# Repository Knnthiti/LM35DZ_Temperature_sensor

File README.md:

# Zero and Span Adjustment Circuit for LM35 Temperature Sensor

โปรเจกต์นี้เป็นการออกแบบและสร้างวงจรปรับแต่งสัญญาณ (Signal Conditioning) เพื่อแปลงแรงดันจากเซนเซอร์ **LM35** ให้เหมาะสมกับ ADC ของ Microcontroller โดยค่าที่ได้จากการทดลองอยู่ในช่วงประมาณ **0.218V – 0.507V** และแปลงเป็นค่า ADC ได้ประมาณ **0.64 – 3.10**

## 📐 รายละเอียดการคำนวณ (Calculation)

ข้อมูลในหัวข้อนี้อ้างอิงจาก **ผลการทดลองจริง** โดยสามารถดูแหล่งข้อมูลได้จากไฟล์ **กราฟการทดลอง.xlsx**

### 1. วิเคราะห์สัญญาณขาเข้า (Input Analysis)
ค่าที่วัดได้จากการทดลองจริงมีดังนี้:

| อุณหภูมิ (°C) | แรงดัน (V) | ADC |
|---:|---:|---:|
| 50 | 0.507 | 3.10 |
| 45 | 0.454 | 2.82 |
| 40 | 0.403 | 2.35 |
| 35 | 0.355 | 1.94 |
| 30 | 0.312 | 1.51 |
| 25 | 0.253 | 1.00 |
| 20 | 0.218 | 0.64 |

### 2. สมการเส้นตรง (Transfer Function)
ใช้รูปแบบสมการเส้นตรงแบบเดิมคือ
$$y = mx + c$$

โดย
- $m$ คือความชัน (Slope)
- $c$ คือจุดตัดแกน $y$ (Offset)

**2.1 การหาสมการ V_to_ADC**

กำหนดให้ $x = V$ และ $y = ADC$

- แทนค่าจากข้อมูลจริงในไฟล์ **กราฟการทดลอง.xlsx** (ใช้จุดปลายช่วงวัด)
  - จุดที่ 1: $(V, ADC) = (0.218, 0.64)$
  - จุดที่ 2: $(V, ADC) = (0.507, 3.10)$

- **หาค่าความชัน (Slope) แบบเดิม:**
  $$m = \frac{\Delta ADC}{\Delta V} = \frac{3.10 - 0.64}{0.507 - 0.218} = \frac{2.46}{0.289} = 8.5121$$

- **หาค่าออฟเซต (Intercept):**
  แทนค่าใน $y = mx + c$ ด้วยจุด $(0.218, 0.64)$
  $$0.64 = (8.5121 \times 0.218) + c$$
  $$0.64 = 1.8556 + c$$
  $$c = 0.64 - 1.8556 = -1.2156$$

- ตรวจสอบกับเส้นแนวโน้ม (Linear Trendline) จะได้ค่าเดียวกันคือ
  $$m = 8.5121,\; c = -1.2156$$

ดังนั้นสมการคือ
$$ADC = 8.5121V - 1.2156$$

**2.2 การหาสมการ ADC_to_C**

กำหนดให้ $x = ADC$ และ $y = C$

- จากการทำเส้นแนวโน้ม (Linear Trendline) ในไฟล์ **กราฟการทดลอง.xlsx** ได้ค่า
  $$m = 11.336,\; c = 13.106$$

ดังนั้นสมการคือ
$$C = 11.336(ADC) + 13.106$$

**สรุปสมการจากข้อมูลทดลองจริง (พร้อมกราฟ):**

1. **V_to_ADC**
   $$ADC = 8.5121V - 1.2156$$

2. **ADC_to_C**
   $$C = 11.336(ADC) + 13.106$$

จากภาพด้านบน ค่าที่ใช้ใน README เป็นค่าจริงจากการทดลอง และสามารถตรวจสอบรายละเอียดได้จากไฟล์ **กราฟการทดลอง.xlsx**

---

## 🛠 โครงสร้างและการทำงานของวงจร

วงจรนี้ใช้ Op-Amp **LM358** ในการจัดการสัญญาณ แบ่งออกเป็นส่วนต่างๆ ดังนี้:

- **Sensor Input:** รับสัญญาณจาก LM35-LP ที่ไฟเลี้ยง 3.3V
- **Input Buffer (U2A):** ทำหน้าที่เป็น Voltage Follower เพื่อแยกโหลดออกจากตัวเซนเซอร์
- **Zero Adjustment (U3A):** ใช้ Potentiometer (RV1) เพื่อปรับแรงดันอ้างอิง (Reference Voltage) สำหรับชดเชยค่า Offset
- **Span Adjustment (U3B):** ปรับอัตราขยาย (Gain) เพื่อให้ได้ช่วงแรงดันที่ต้องการ (Span)
- **Output:** สัญญาณ $V_{out}$ จะถูกส่งออกทาง Connector J1

## 📊 ระบบแสดงข้อมูล (Display System)

ระบบแสดงผลถูกแบ่งเป็น 3 โหมดตามปุ่มควบคุม ดังนี้:
- **ปุ่มซ้าย:** เข้าโหมด **WiFi Manager** และเมื่อเชื่อมต่อเครือข่ายสำเร็จ ระบบจะแสดง **IP Address** สำหรับเชื่อมต่อผ่าน **WebSocket**
- **ปุ่มกลาง:** แสดงค่า **อุณหภูมิ** ที่วัดได้จากเซนเซอร์
- **ปุ่มขวา:** แสดงค่า **แรงดันไฟฟ้า** ของสัญญาณที่วัดได้

เป็น Zero and span adjustment circuit :
- **R ตัวบน:** เป็น Rf ปรับกำลังขยาย
- **R ตัวล่าง:** เป็น span ปรับแรงดัน

โค้ดโปรแกรมสามารถดูได้ที่ไฟล์ `T_sensor_V3/T_sensor_V3.ino`

---

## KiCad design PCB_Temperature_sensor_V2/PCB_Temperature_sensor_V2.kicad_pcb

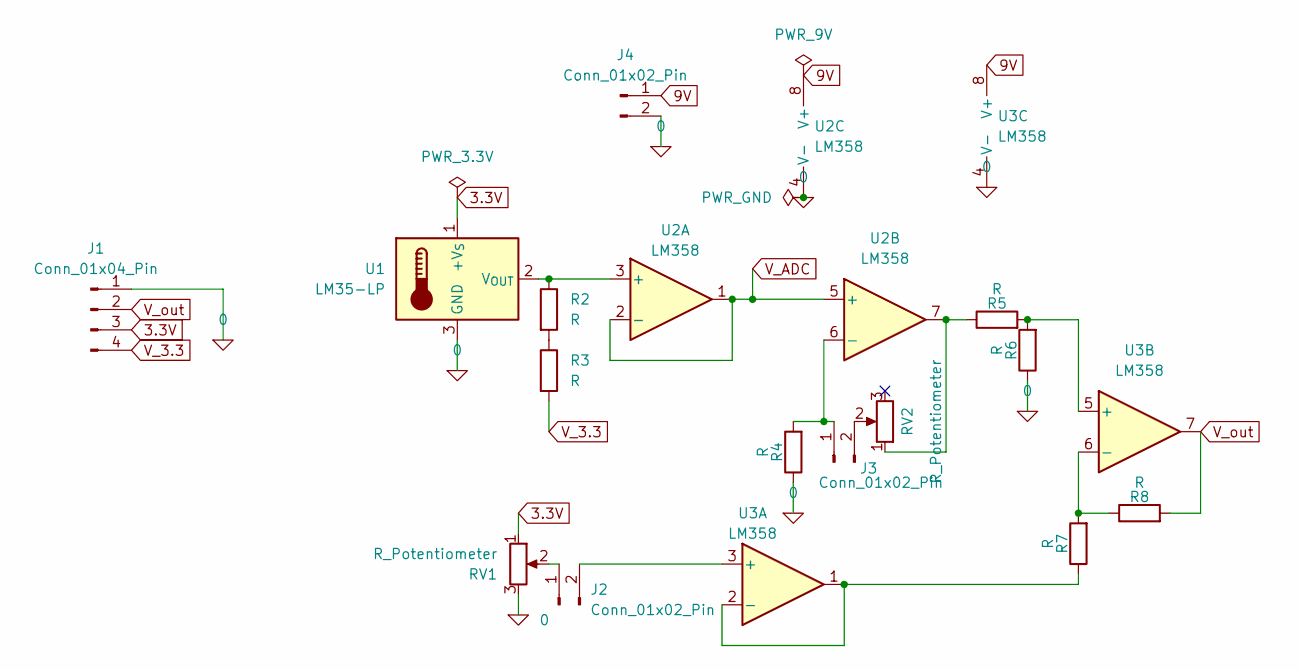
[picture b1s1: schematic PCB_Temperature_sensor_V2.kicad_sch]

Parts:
J1: Conn_01x04_Pin; PinSocket_1x04_P2.54mm_Vertical
J2, J3, J4: Conn_01x02_Pin; PinHeader_1x02_P2.54mm_Vertical
R2, R3: R; R_Axial_DIN0207_L6.3mm_D2.5mm_P7.62mm_Horizontal
R4, R5, R6, R7, R8: R; R_0603_1608Metric_Pad0.98x0.95mm_HandSolder
RV1, RV2: R_Potentiometer; Potentiometer_Piher_PT-10-V10_Vertical
U1: LM35-LP; TO-92_Inline
U2, U3: LM358; DIP-8_W7.62mm

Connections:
0: J1.1, J4.2, R4.1, R6.1, RV1.3, U1.3 (GND), U2.4 (V-), U3.4 (V-)
3.3V: J1.3, RV1.1, U1.1 (+V_{S})
9V: J4.1, U2.8 (V+), U3.8 (V+)
unnamed: J2.1, RV1.2
unnamed: J2.2, U3.3 (+)
unnamed: J3.1, R4.2, U2.6 (-)
unnamed: J3.2, RV2.2
unnamed: R2.2, R3.1
unnamed: R5.1, RV2.1, U2.7
unnamed: R2.1, U1.2 (V_{OUT}), U2.3 (+)
unnamed: R7.1, U3.1, U3.2 (-)
unnamed: R5.2, R6.2, U3.5 (+)
unnamed: R7.2, R8.1, U3.6 (-)
V_3.3: J1.4, R3.2
V_ADC: U2.1, U2.2 (-), U2.5 (+)
V_out: J1.2, R8.2, U3.7

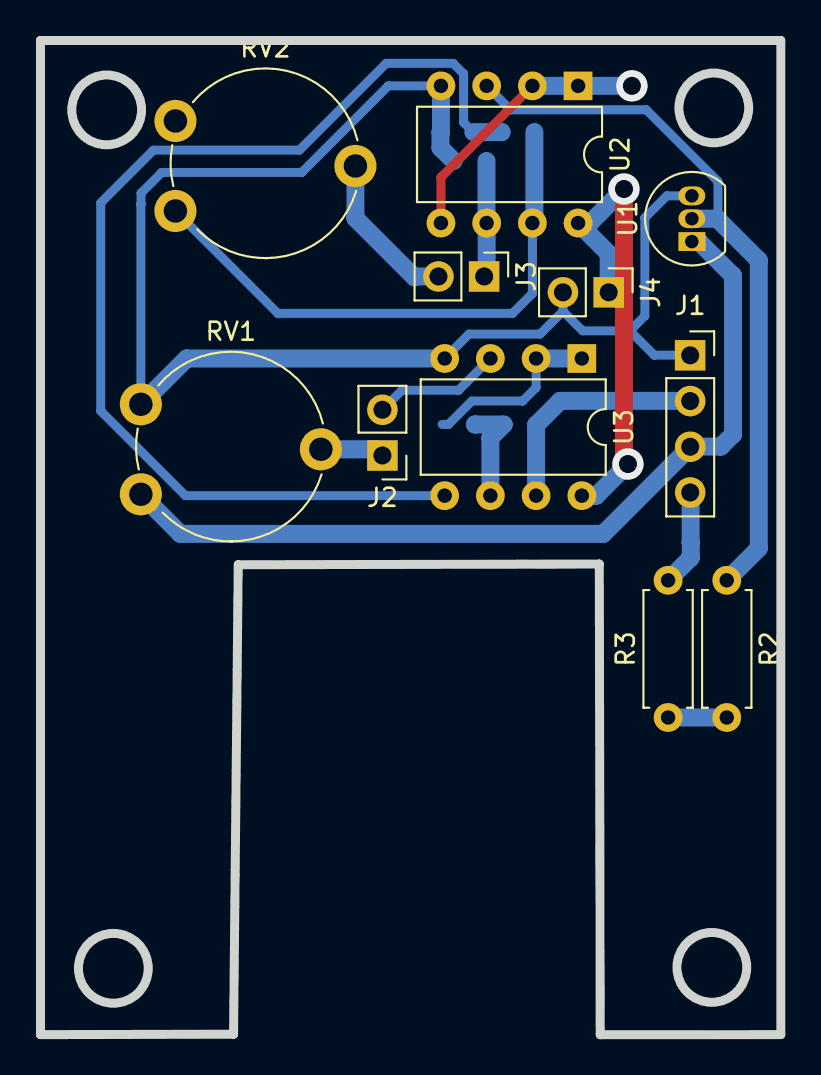
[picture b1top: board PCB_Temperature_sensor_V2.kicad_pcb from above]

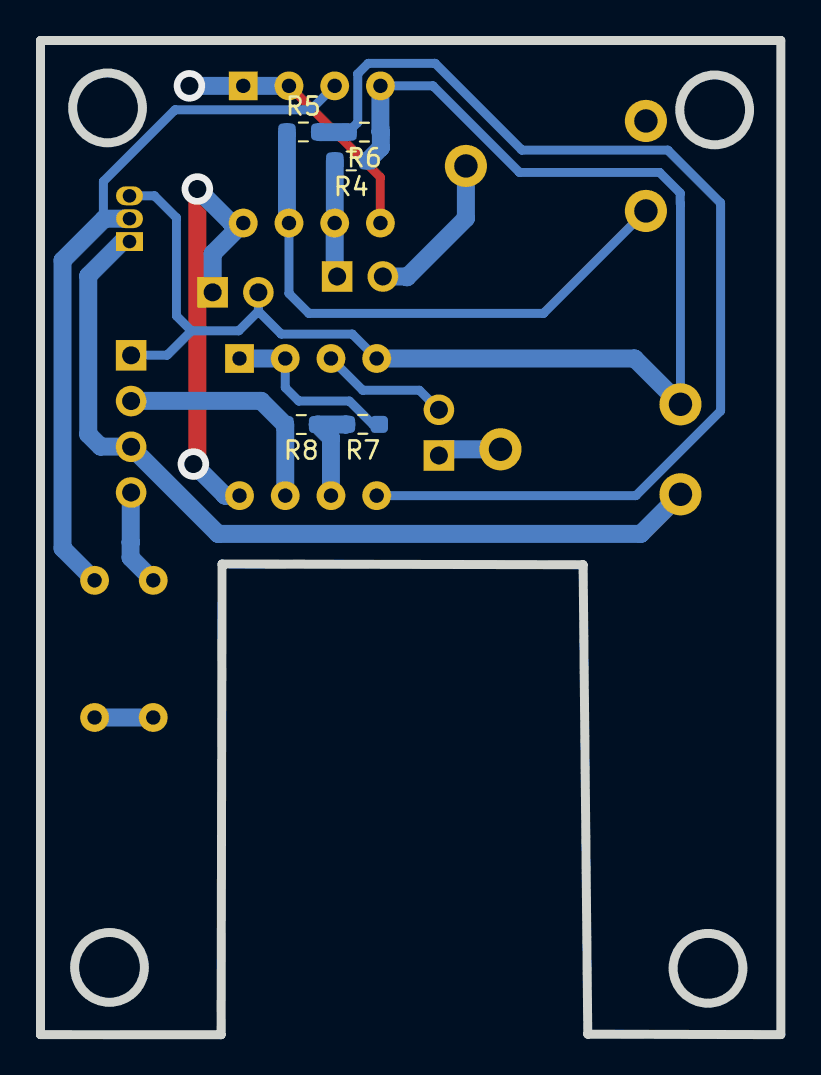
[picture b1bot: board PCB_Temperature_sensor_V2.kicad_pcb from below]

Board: 2 copper layers, 41.1 x 55.2 mm, 16 parts (5 on the bottom side), 16 nets.

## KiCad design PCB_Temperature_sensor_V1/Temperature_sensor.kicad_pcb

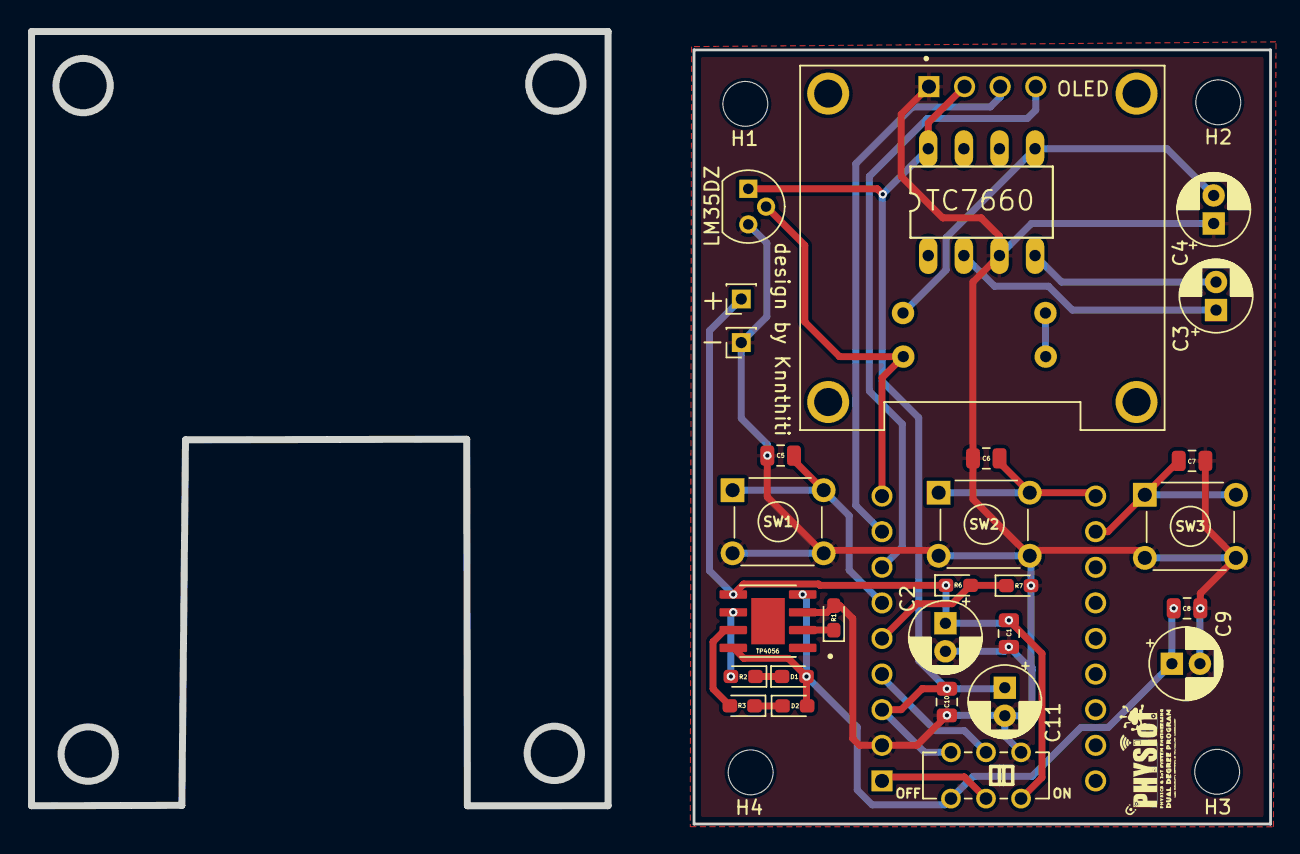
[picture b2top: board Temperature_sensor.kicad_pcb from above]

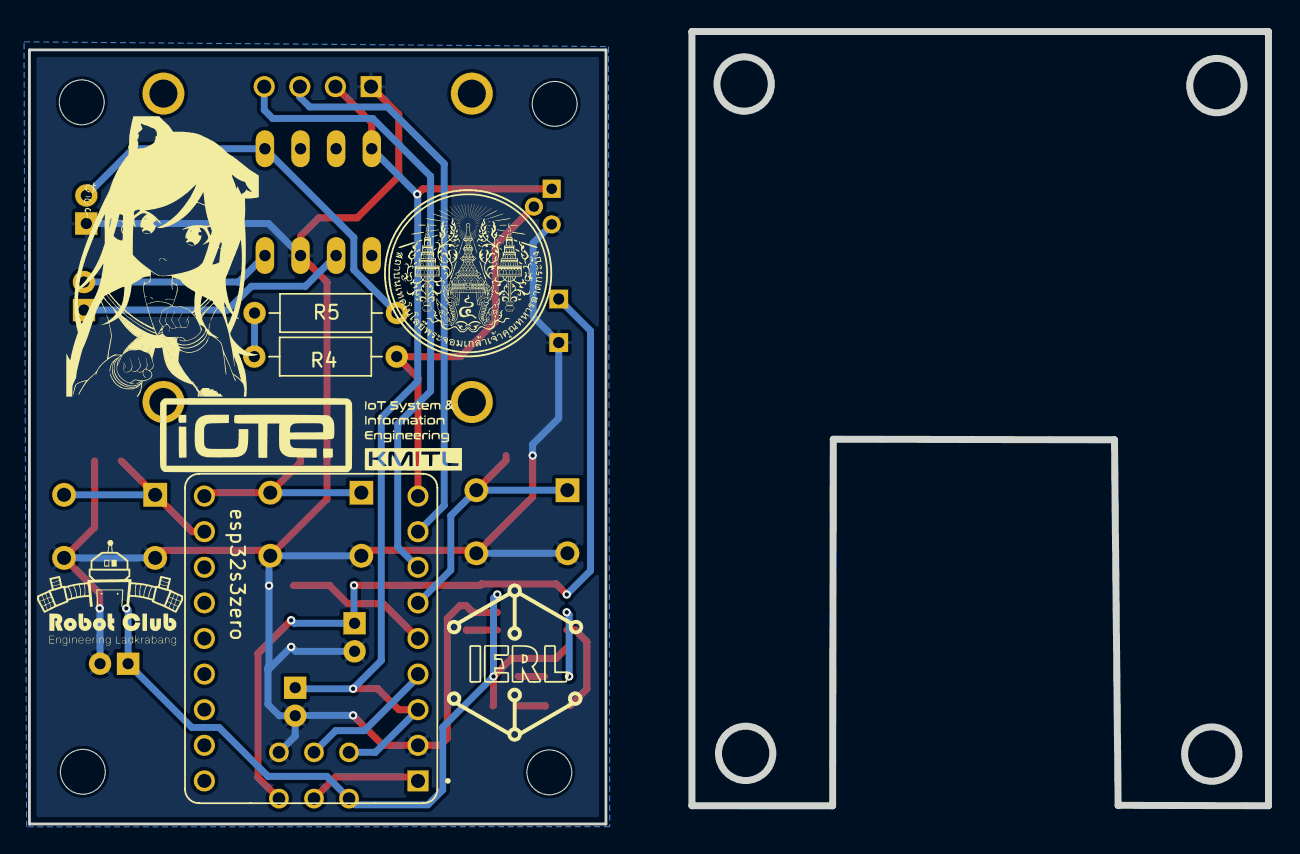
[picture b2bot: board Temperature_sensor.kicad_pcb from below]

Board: 2 copper layers, 88.2 x 56.4 mm, 35 parts (3 on the bottom side), 22 nets.

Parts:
+: BAT_3.7V; PinSocket_1x01_P2.00mm_Vertical
-: BAT_GND; PinSocket_1x01_P2.00mm_Vertical
C1, C5, C6, C7, C8, C10: 0.1uC; C_0805_2012Metric
C2, C9, C11: 22uC; CP_Radial_D5.0mm_P2.00mm
C3, C4: 10uC; CP_Radial_D5.0mm_P2.00mm
D1: LED_Green; LED_0603_1608Metric_Pad1.05x0.95mm_HandSolder
D2: LED_Red; LED_0603_1608Metric_Pad1.05x0.95mm_HandSolder
H1, H2, H3, H4: MountingHole; MountingHole_3.2mm_M3
LM35DZ: LM35-LP; TO-92
OFF                   ON: JS202011CQN
OLED: DM-OLED096-636; MODULE_DM-OLED096-636
R1, R2, R3, R6, R7: 1k; LED_0603_1608Metric_Pad1.05x0.95mm_HandSolder
R4: 47k; R_Axial_DIN0207_L6.3mm_D2.5mm_P10.16mm_Horizontal
R5: 20k; R_Axial_DIN0207_L6.3mm_D2.5mm_P10.16mm_Horizontal
SW1, SW2, SW3: SW_Push; SW_TH_Tactile_Omron_B3F-10xx
TC7660: TC7660
TP4056: TP4056; SOP127P600X175-9N
esp32s3zero: ESP32-S3-ZERO; MODULE_ESP32-S3-ZERO

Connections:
0: -.1, C1.2, C2.2, C4.1, C5.2, C6.2, C7.2, C8.2, C9.2, C10.2, C11.2, LM35DZ.3 (GND), OFF ON.4, OLED.1 (GND), R1.2, R7.2, SW1.2, SW2.2, SW3.2, TC7660.3 (GND), TP4056.3 (GND), esp32s3zero.GND
3.3V: C10.1, C11.1, LM35DZ.1 (+V_{S}), OFF ON.6, OLED.2 (VCC_IN), TC7660.8 (V+), esp32s3zero.3V3 (3V3(OUT))
5V: C8.1, C9.1, D1.2 (A), D2.2 (A), OFF ON.3, TP4056.4 (VCC), TP4056.8 (CE)
ADC: LM35DZ.2 (V_{OUT}), R4.1, esp32s3zero.6 (GP6)
BAT: +.1, C1.1, C2.1, OFF ON.1, R6.1, TP4056.5 (BAT)
Chek_BAT: R6.2, R7.1, esp32s3zero.2 (GP2)
GP1: OFF ON.5, esp32s3zero.1 (GP1)
GP3: C5.1, SW1.1, esp32s3zero.3 (GP3)
GP7: C6.1, SW2.1, esp32s3zero.7 (GP7)
GP8: C7.1, SW3.1, esp32s3zero.8 (GP8)
unnamed: D1.1 (K), R2.1
unnamed: D2.1 (K), R3.1
unnamed: C3.1, TC7660.2 (CAP+)
unnamed: C3.2, TC7660.4 (CAP-)
unnamed: C4.2, R5.2, TC7660.5 (VOUT)
unnamed: R4.2, R5.1
unnamed: OFF ON.2, esp32s3zero.5V
unnamed: R1.1, TP4056.2 (PROG)
unnamed: R3.2, TP4056.7 (~CHRG)
unnamed: R2.2, TP4056.6 (~STDBY)
SCL: OLED.3 (SCL), esp32s3zero.5 (GP5)
SDA: OLED.4 (SDA), esp32s3zero.4 (GP4)

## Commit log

2026-02-07 final
2026-02-09 pdf_V2
2026-02-15 codeV2
2026-02-20 V2_amp
2026-03-05 Add README for LM35 Signal Conditioning Circuit
    Added project details and circuit design for LM35 temperature sensor signal conditioning.
2026-03-05 add datasheet
2026-03-07 new code
